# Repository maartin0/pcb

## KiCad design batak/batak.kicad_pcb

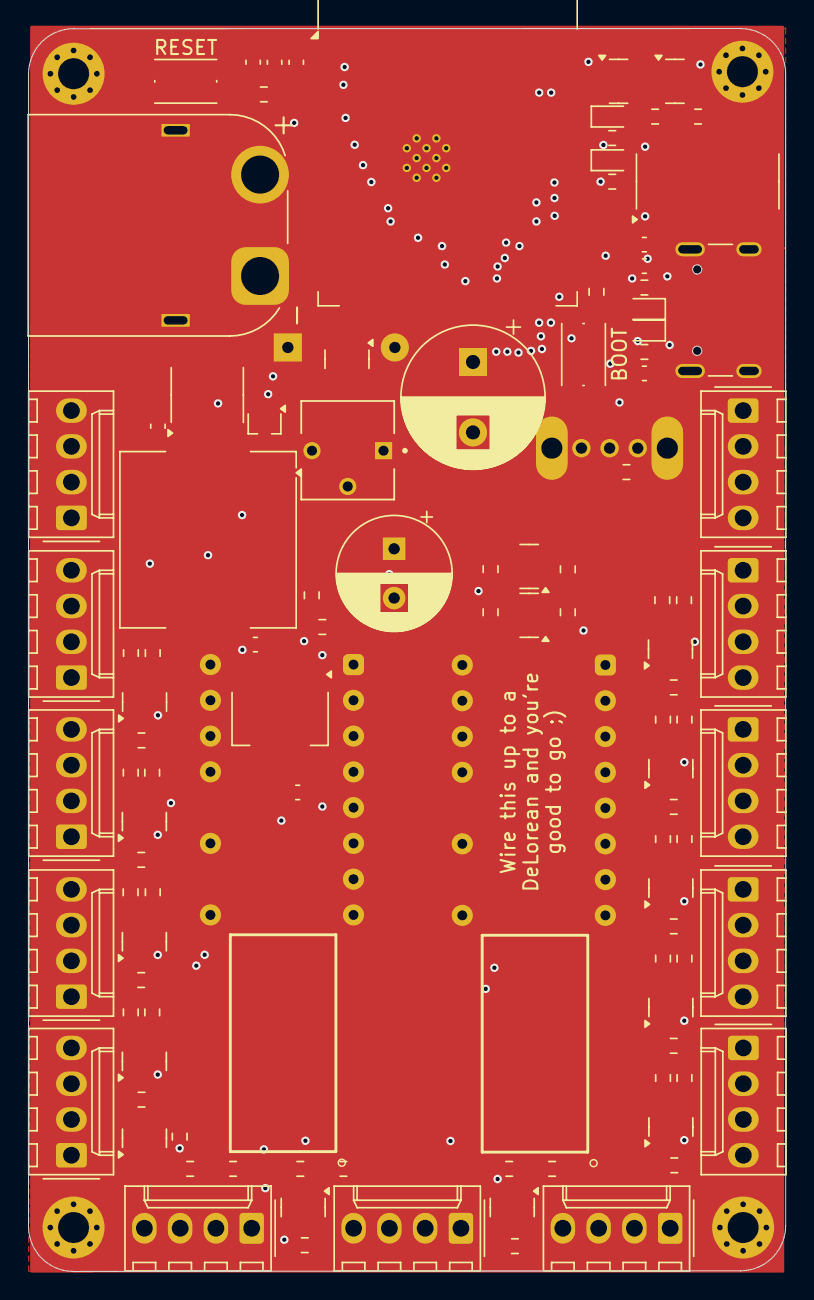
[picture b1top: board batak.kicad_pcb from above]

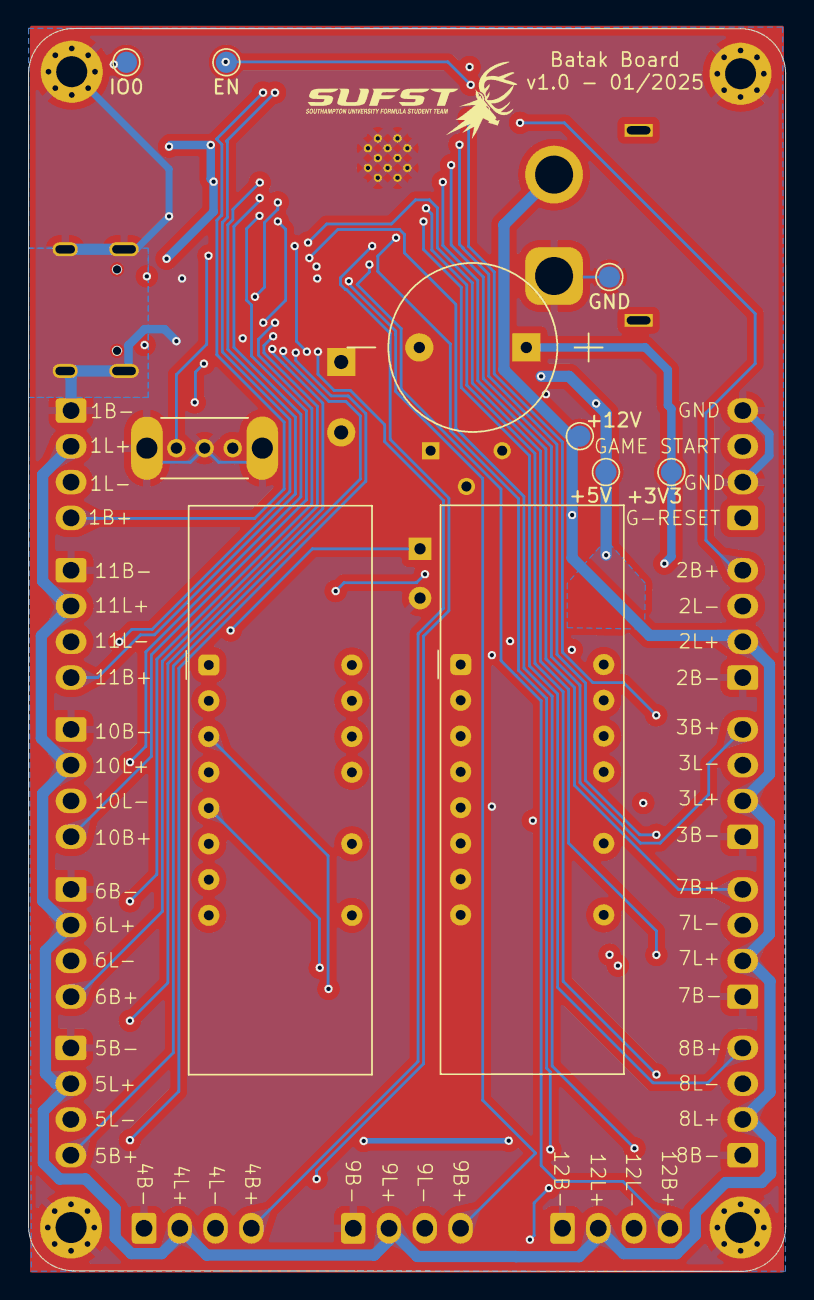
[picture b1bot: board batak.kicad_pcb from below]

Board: 4 copper layers, 53.8 x 88.3 mm, 123 parts (10 on the bottom side), 104 nets.

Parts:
BZ1: Buzzer; CUI_CMI-1275-85T
C1, C3, C4, C7, C8, C10: 10uF; C_0603_1608Metric
C2: 10nF; C_0603_1608Metric
C5: 470uF; CP_Radial_D10.0mm_P5.00mm
C6, C9: 100nF; C_0603_1608Metric
C11: 180uF; CP_Radial_D8.0mm_P3.50mm
D1: YELLOW; LED_0603_1608Metric
D2: GREEN; LED_0603_1608Metric
D3, D4: ESD9B3.3ST5G; D_0603_1608Metric
D5: BAT54W; SOT-323_SC-70
H1, H2, H3, H4: MountingHole_Pad; MountingHole_2.2mm_M2_Pad_Via
IC1, IC2: HT16K33
J1: USB_C_Receptacle_USB2.0_16P; USB_C_Receptacle_GCT_USB4105-xx-A_16P_TopMnt_Horizontal
J2, J3, J4, J5, J6, J7, J8, J9, J10, J11, J12, J13, J15: Molex_KK-254; Molex_KK-254_AE-6410-04A_1x04_P2.54mm_Vertical
J14: Conn_01x02; AMASS_XT60PW-M_1x02_P7.20mm_Horizontal
L1: 68uH; L_Coilcraft_MSS1210-XXX
Q1, Q2: NPN; SOT-23
Q3, Q4, Q5, Q6, Q7, Q8, Q9, Q10, Q11, Q12, Q13, Q14, Q15, Q16, Q17: NMOS; SOT-23
R1, R2, R40, R41, R42, R43, R44, R45, R46, R47, R48, R49, R50, R51: 1k; R_0603_1608Metric
R3, R4, R5, R8, R9, R22, R23, R24, R25, R26, R27, R28, R29, R30, R31, R32, R33, R34, R35, R36, R37: 10k; R_0603_1608Metric
R6, R7: 5.1k; R_0603_1608Metric
R10, R11, R12, R13, R14, R15, R16, R17, R18, R19, R20, R21, R38, R39: 51k; R_0603_1608Metric
RV1: 300k; TRIM_3362P-1-304LF
SW1: BOOT; SW_Push_1P1T_NO_CK_KMR2
SW2: RESET; SW_Push_1P1T_NO_CK_KMR2
SW3: 0S102011MS2QN1
TP1: GND; TestPoint_Pad_D1.5mm
TP2: +3V3; TestPoint_Pad_D1.5mm
TP3: +5V; TestPoint_Pad_D1.5mm
TP4: +12V; TestPoint_Pad_D1.5mm
TP7: IO0; TestPoint_Pad_D1.5mm
TP8: EN; TestPoint_Pad_D1.5mm
U2: CH340C; SOIC-16_3.9x9.9mm_P1.27mm
U3: XL1509-5.0; SOIC-8_3.9x4.9mm_P1.27mm
U4: ESP32-S3-WROOM-1
U5, U6: LTC-4627JR; LTC-4627Jx
U7: AZ1117CH-3.3TRG1; SOT-223-3_TabPin2

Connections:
+3V3: BZ1.1 (+), C3.1, C4.2, C9.1, C10.2, Q15.2 (G), Q16.2 (G), R1.2, R2.2, R5.2, R8.2, R9.1, R10.2, R11.2, R12.2, R13.2, R14.2, R15.2, R16.2, R17.2, R18.2, R19.2, R20.2, R21.2, R35.1, R37.1, R38.2, R39.2, RV1.3, TP2.1, U2.16 (VCC), U4.2 (3V3), U7.2 (VO)
+5V: C1.2, C6.2, C11.1, IC1.24 (VDD), IC2.24 (VDD), J1.A4 (VBUS), J1.A9 (VBUS), J1.B4 (VBUS), J1.B9 (VBUS), L1.2, R34.1, R36.1, TP3.1, U3.3 (FB), U7.3 (VI)
+12V: C5.1, C7.1, J2.2, J3.2, J4.2, J5.2, J6.2, J7.2, J8.2, J9.2, J10.2, J11.2, J12.2, J13.2, J14.2, TP4.1, U3.1 (VIN)
/4 digit 7 segment display1/COM1: IC2.3 (COM1/KS0), U6.1 (CA1)
/4 digit 7 segment display1/COM2: IC2.4 (COM2/KS1), U6.2 (CA2)
/4 digit 7 segment display1/COM3: IC2.5 (COM3/KS2), U6.6 (CA3)
/4 digit 7 segment display1/COM4: IC2.6 (COM4), U6.8 (CA4)
/4 digit 7 segment display1/COM5: IC2.7 (COM5), U6.4 (CAL)
/4 digit 7 segment display1/K1: IC2.19 (ROW2/K1), U6.14 (A)
/4 digit 7 segment display1/K2: IC2.18 (ROW3/K2), U6.16 (B)
/4 digit 7 segment display1/K3: IC2.17 (ROW4/K3), U6.13 (C)
/4 digit 7 segment display1/K4: IC2.16 (ROW5/K4), U6.3 (D)
/4 digit 7 segment display1/K5: IC2.15 (ROW6/K5), U6.5 (E)
/4 digit 7 segment display1/K6: IC2.14 (ROW7/K6), U6.11 (F)
/4 digit 7 segment display1/K7: IC2.13 (ROW8/K7), U6.15 (G)
/4 digit 7 segment display1/K8: IC2.12 (ROW9/K8), U6.7 (DP)
/4 digit 7 segment display/COM1: IC1.3 (COM1/KS0), U5.1 (CA1)
/4 digit 7 segment display/COM2: IC1.4 (COM2/KS1), U5.2 (CA2)
/4 digit 7 segment display/COM3: IC1.5 (COM3/KS2), U5.6 (CA3)
/4 digit 7 segment display/COM4: IC1.6 (COM4), U5.8 (CA4)
/4 digit 7 segment display/COM5: IC1.7 (COM5), U5.4 (CAL)
/4 digit 7 segment display/K1: IC1.19 (ROW2/K1), U5.14 (A)
/4 digit 7 segment display/K2: IC1.18 (ROW3/K2), U5.16 (B)
/4 digit 7 segment display/K3: IC1.17 (ROW4/K3), U5.13 (C)
/4 digit 7 segment display/K4: IC1.16 (ROW5/K4), U5.3 (D)
/4 digit 7 segment display/K5: IC1.15 (ROW6/K5), U5.5 (E)
/4 digit 7 segment display/K6: IC1.14 (ROW7/K6), U5.11 (F)
/4 digit 7 segment display/K7: IC1.13 (ROW8/K7), U5.15 (G)
/4 digit 7 segment display/K8: IC1.12 (ROW9/K8), U5.7 (DP)
/BTN_1_LIGHT: Q4.2 (G), R23.2, U4.39 (IO1)
/BTN_1_OUTPUT: J3.4, R11.1, U4.38 (IO2)
/BTN_2_LIGHT: Q5.2 (G), R24.2, U4.4 (IO4)
/BTN_2_OUTPUT: J4.4, R12.1, U4.5 (IO5)
/BTN_3_LIGHT: Q6.2 (G), R25.2, U4.6 (IO6)
/BTN_3_OUTPUT: J5.4, R13.1, U4.7 (IO7)
/BTN_4_LIGHT: Q7.2 (G), R26.2, U4.12 (IO8)
/BTN_4_OUTPUT: J6.4, R14.1, U4.17 (IO9)
/BTN_5_LIGHT: Q8.2 (G), R27.2, U4.18 (IO10)
/BTN_5_OUTPUT: J7.4, R15.1, U4.19 (IO11)
/BTN_6_LIGHT: Q9.2 (G), R28.2, U4.20 (IO12)
/BTN_6_OUTPUT: J8.4, R16.1, U4.21 (IO13)
/BTN_7_LIGHT: Q10.2 (G), R29.2, U4.22 (IO14)
/BTN_7_OUTPUT: J9.4, R17.1, U4.8 (IO15)
/BTN_8_LIGHT: Q11.2 (G), R30.2, U4.9 (IO16)
/BTN_8_OUTPUT: J10.4, R18.1, U4.10 (IO17)
/BTN_9_LIGHT: Q12.2 (G), R31.2, U4.11 (IO18)
/BTN_9_OUTPUT: J11.4, R19.1, U4.14 (IO20)
/BTN_10_LIGHT: Q13.2 (G), R32.2, U4.23 (IO21)
/BTN_10_OUTPUT: J12.4, R20.1, U4.31 (IO38)
/BTN_11_LIGHT: Q14.2 (G), R33.2, U4.32 (IO39)
/BTN_11_OUTPUT: J13.4, R21.1, U4.33 (IO40)
/BTN_12_LIGHT: Q3.2 (G), R22.2, U4.28 (IO35)
/BTN_12_OUTPUT: J2.4, R10.1, U4.13 (IO19)
/BUZZER: Q17.2 (G), U4.29 (IO36)
/DTR: Q1.3 (E), R4.1, U2.13 (~DTR)
/EN: C8.2, Q2.1 (C), R5.1, SW2.1, TP8.1, U4.3 (EN)
/GAME_RESET: J15.1, R39.1, U4.24 (IO47)
/GAME_START: J15.3, R38.1, U4.25 (IO48)
/IO0: Q1.1 (C), R8.1, SW1.1, TP7.1, U4.27 (IO0)
/RTS: Q2.3 (E), R3.1, U2.14 (~RTS)
/RX: D2.1 (K), U2.3 (RXD), U4.37 (TXD0)
/RX0: D1.1 (K), U2.2 (TXD), U4.36 (RXD0)
/SCL: Q16.3 (S), R35.2, U4.35 (IO42)
/SCL_5V: IC1.22 (SCL), IC2.22 (SCL), Q16.1 (D), R36.2
/SDA: Q15.3 (S), R9.2, U4.34 (IO41)
/SDA_5V: IC1.23 (SDA), IC2.23 (SDA), Q15.1 (D), R34.2
/TOGGLE_SW: R37.2, SW3.3 (C), U4.30 (IO37)
/USB_D+: D4.1 (A1), J1.A6 (D+), J1.B6 (D+), U2.5 (UD+)
/USB_D-: D3.1 (A1), J1.A7 (D-), J1.B7 (D-), U2.6 (UD-)
/VOLUME_POT: RV1.2, U4.15 (IO3)
GND: C1.1, C2.2, C3.2, C4.1, C5.2, C6.1, C7.2, C8.1, C9.2, C10.1, C11.2, D3.2 (A2), D4.2 (A2), D5.1 (A), H1.1, H2.1, H3.1, H4.1, IC1.1 (VSS), IC2.1 (VSS), J1.A1 (GND), J1.A12 (GND), J1.B1 (GND), J1.B12 (GND), J1.S1 (SHIELD), J2.1, J3.1, J4.1, J5.1, J6.1, J7.1, J8.1, J9.1, J10.1, J11.1, J12.1, J13.1, J14.1, J15.2, J15.4, Q3.3 (S), Q4.3 (S), Q5.3 (S), Q6.3 (S), Q7.3 (S), Q8.3 (S), Q9.3 (S), Q10.3 (S), Q11.3 (S), Q12.3 (S), Q13.3 (S), Q14.3 (S), Q17.3 (S), R6.1, R7.1, R22.1, R23.1, R24.1, R25.1, R26.1, R27.1, R28.1, R29.1, R30.1, R31.1, R32.1, R33.1, RV1.1, SW1.2, SW2.2, SW3.2 (B), SW3.4 (BASE), SW3.5 (BASE), TP1.1, U2.1 (GND), U3.4 (~EN), U3.5 (GND), U3.6 (GND), U3.7 (GND), U3.8 (GND), U4.1 (GND), U4.40 (GND), U4.41 (GND), U7.1 (GND)
unnamed: BZ1.2 (-), Q17.1 (D)
unnamed: D1.2 (A), R1.1
unnamed: D2.2 (A), R2.1
unnamed: D5.3 (K), L1.1, U3.2 (OUT)
unnamed: J1.A5 (CC1), R7.2
unnamed: J1.B5 (CC2), R6.2
unnamed: J2.3, R40.2
unnamed: J3.3, R41.2
unnamed: J4.3, R42.2
unnamed: J5.3, R43.2
unnamed: J6.3, R44.2
unnamed: J7.3, R45.2
unnamed: J8.3, R46.2
unnamed: J9.3, R47.2
unnamed: J10.3, R48.2
unnamed: J11.3, R49.2
unnamed: J12.3, R50.2
unnamed: J13.3, R51.2
unnamed: Q1.2 (B), R3.2
unnamed: Q2.2 (B), R4.2
unnamed: Q3.1 (D), R40.1
unnamed: Q4.1 (D), R41.1
unnamed: Q5.1 (D), R42.1
unnamed: Q6.1 (D), R43.1
unnamed: Q7.1 (D), R44.1
unnamed: Q8.1 (D), R45.1
unnamed: Q9.1 (D), R46.1
unnamed: Q10.1 (D), R47.1
unnamed: Q11.1 (D), R48.1
unnamed: Q12.1 (D), R49.1
unnamed: Q13.1 (D), R50.1
unnamed: Q14.1 (D), R51.1
unnamed: C2.1, U2.4 (V3)

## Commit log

2025-02-25 tag generated release files
2025-02-27 Refactor action to generate production files
2025-02-27 Add more copper to help with heat dissipation :P
2025-02-27 Generate batak production files
